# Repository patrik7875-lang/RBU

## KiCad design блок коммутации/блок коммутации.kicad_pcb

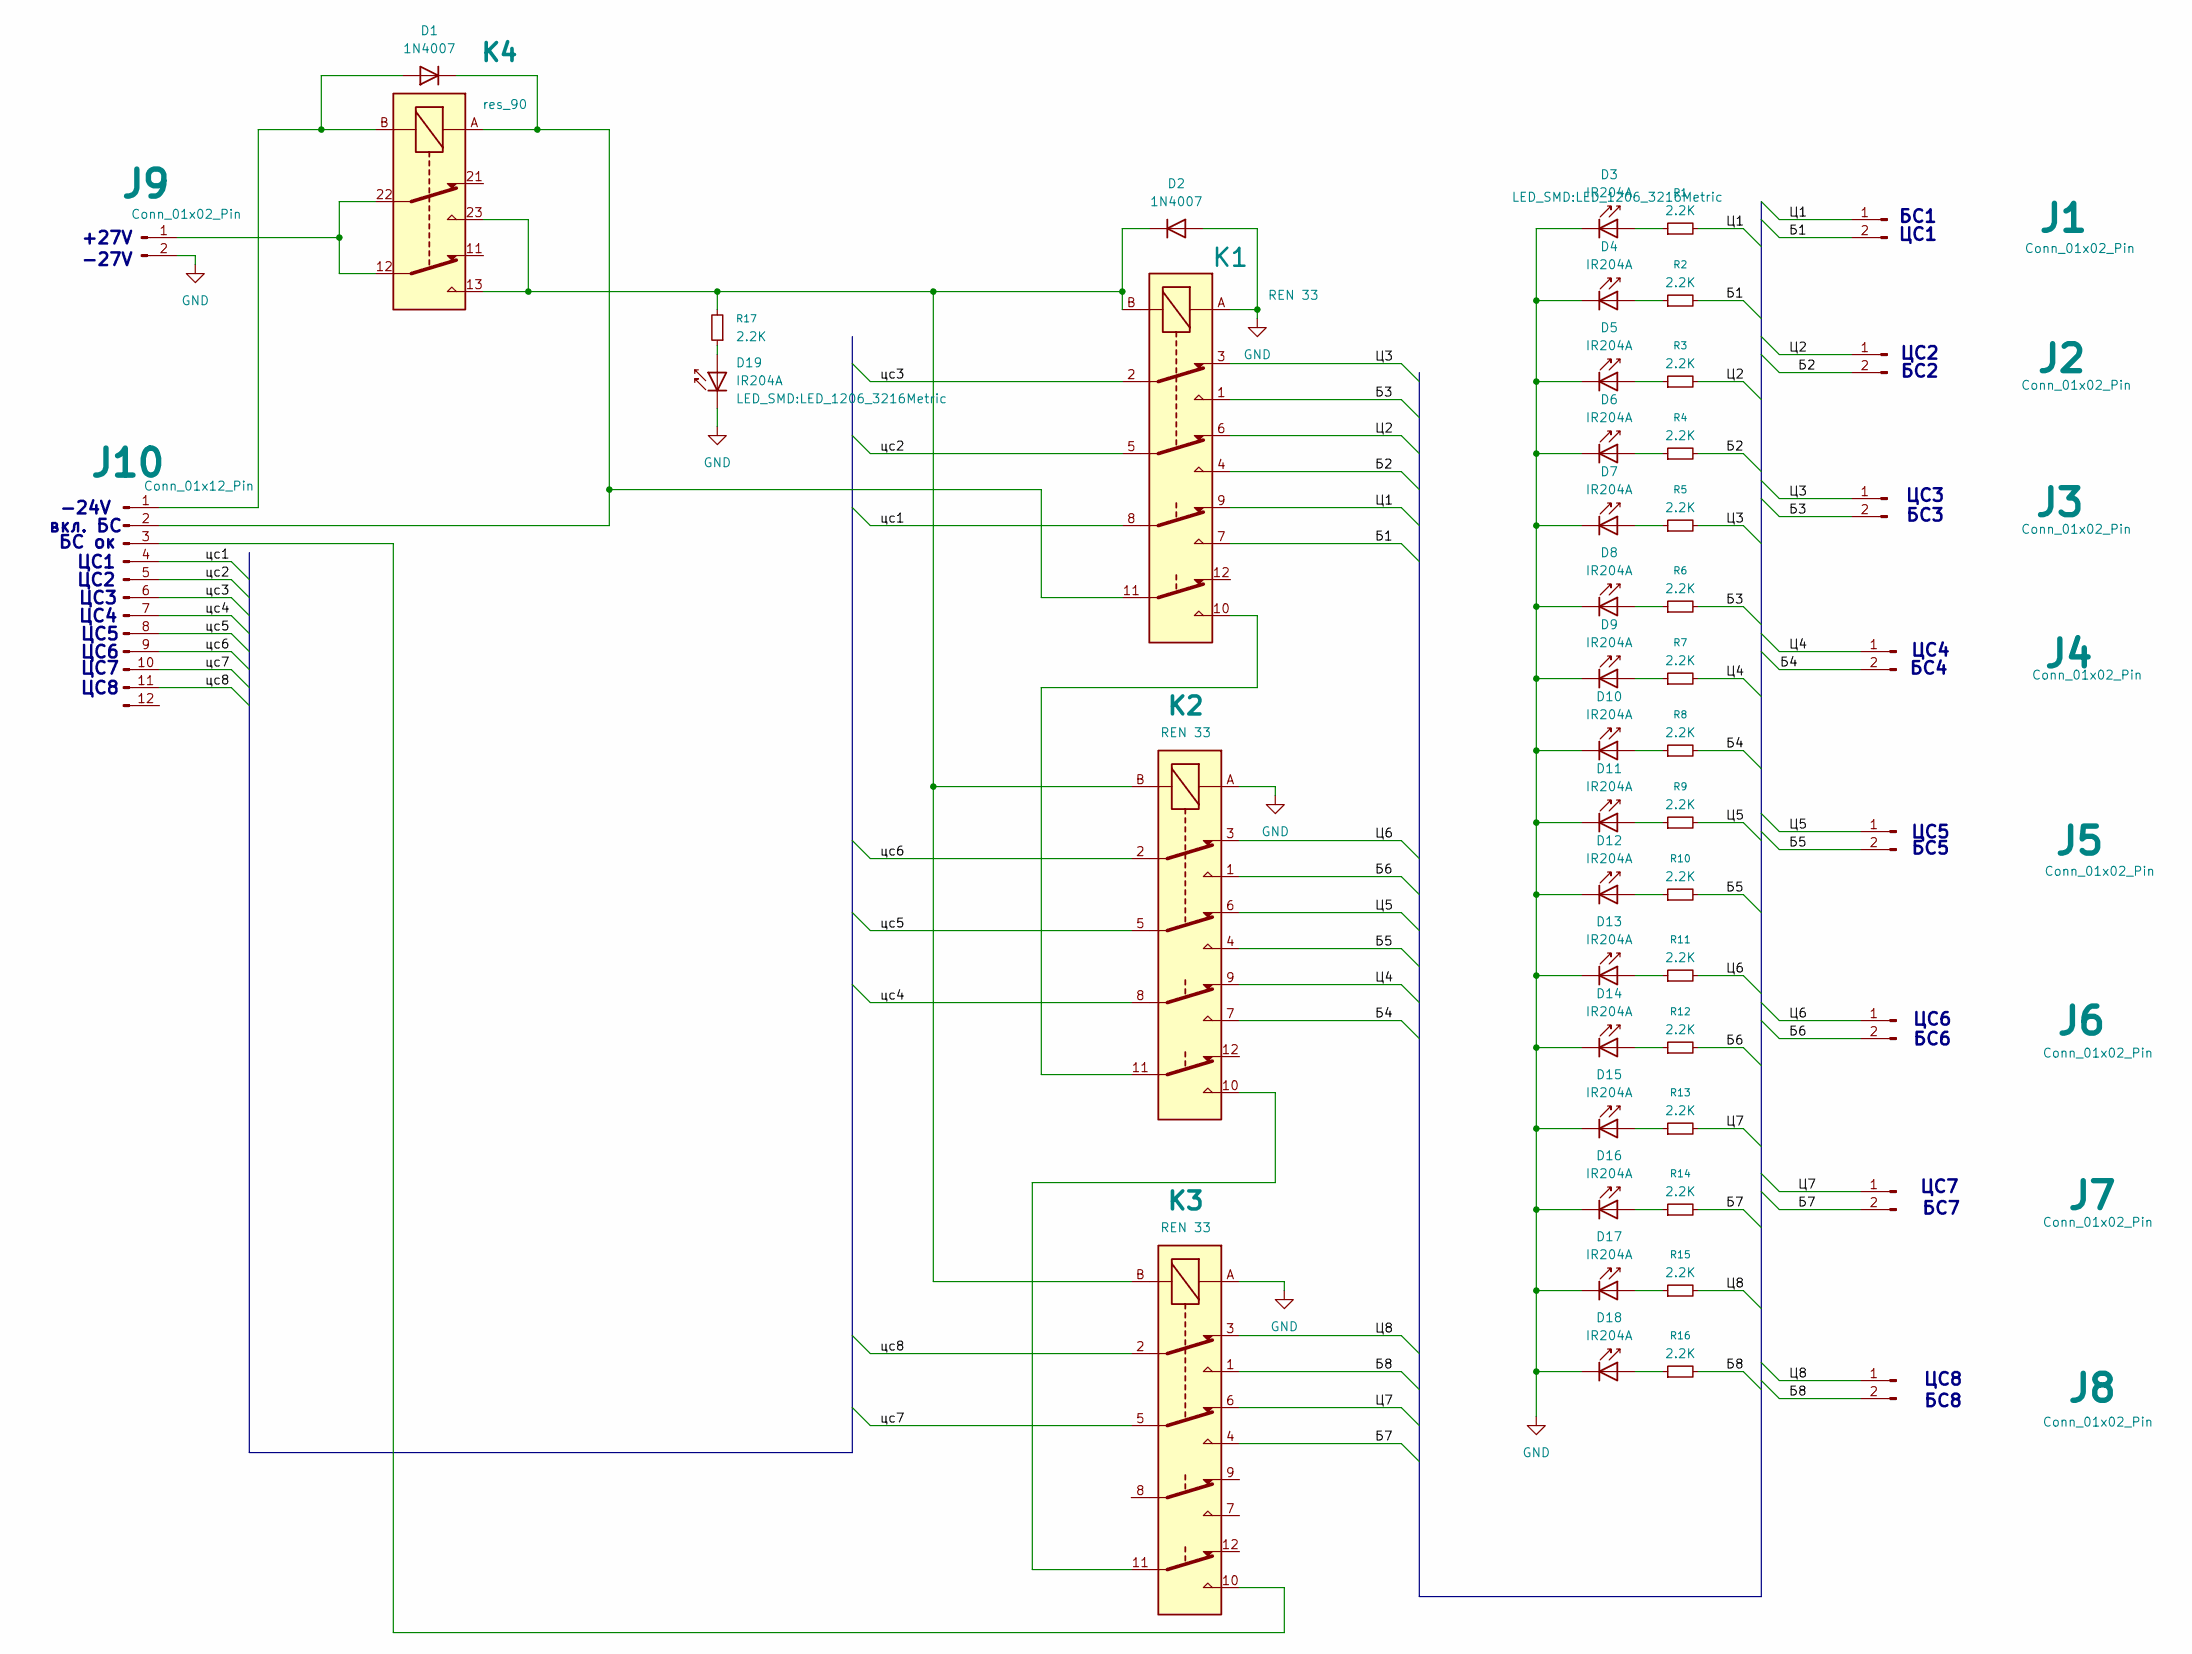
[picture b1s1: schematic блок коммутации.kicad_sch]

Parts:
D1, D2: 1N4007; D_DO-41_SOD81_P10.16mm_Horizontal
D3, D4, D5, D6, D7, D8, D9, D10, D11, D12, D13, D14, D15, D16, D17, D18, D19: IR204A; LED_1206_3216Metric
J1, J2, J3, J4, J5, J6, J7, J8, J9: Conn_01x02_Pin; TerminalBlock_Phoenix_MKDS-1,5-2_1x02_P5.00mm_Horizontal
J10: Conn_01x12_Pin; TerminalBlock_Phoenix_PT-1,5-12-5.0-H_1x12_P5.00mm_Horizont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
K1, K2, K3: REN 33
K4: res_90; res90
R1, R2, R3, R4, R5, R6, R7, R8, R9, R10, R11, R12, R13, R14, R15, R16, R17: 2.2K; R_1206_3216Metric

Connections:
/Б1: J1.2, K1.7, R2.2
/Б2: J2.2, K1.4, R4.2
/Б3: J3.2, K1.1, R6.2
/Б4: J4.2, K2.7, R8.2
/Б5: J5.2, K2.4, R10.2
/Б6: J6.2, K2.1, R12.2
/Б7: J7.2, K3.4, R14.2
/Б8: J8.2, K3.1, R16.2
/Ц1: J1.1, K1.9, R1.2
/Ц2: J2.1, K1.6, R3.2
/Ц3: J3.1, K1.3, R5.2
/Ц4: J4.1, K2.9, R7.2
/Ц5: J5.1, K2.6, R9.2
/Ц6: J6.1, K2.3, R11.2
/Ц7: J7.1, K3.6, R13.2
/Ц8: J8.1, K3.3, R15.2
/цс1: J10.4, K1.8
/цс2: J10.5, K1.5
/цс3: J10.6, K1.2
/цс4: J10.7, K2.8
/цс5: J10.8, K2.5
/цс6: J10.9, K2.2
/цс7: J10.10, K3.5
/цс8: J10.11, K3.2
GND: D2.2 (A), D3.1 (K), D4.1 (K), D5.1 (K), D6.1 (K), D7.1 (K), D8.1 (K), D9.1 (K), D10.1 (K), D11.1 (K), D12.1 (K), D13.1 (K), D14.1 (K), D15.1 (K), D16.1 (K), D17.1 (K), D18.1 (K), D19.1 (K), J9.2, K1.A, K2.A, K3.A
unnamed: D1.2 (A), J10.1, K4.B
unnamed: D1.1 (K), J10.2, K1.11, K4.A
unnamed: D2.1 (K), K1.B, K2.B, K3.B, K4.13, K4.23, R17.2
unnamed: D3.2 (A), R1.1
unnamed: D4.2 (A), R2.1
unnamed: D5.2 (A), R3.1
unnamed: D6.2 (A), R4.1
unnamed: D7.2 (A), R5.1
unnamed: D8.2 (A), R6.1
unnamed: D9.2 (A), R7.1
unnamed: D10.2 (A), R8.1
unnamed: D11.2 (A), R9.1
unnamed: D12.2 (A), R10.1
unnamed: D13.2 (A), R11.1
unnamed: D14.2 (A), R12.1
unnamed: D15.2 (A), R13.1
unnamed: D16.2 (A), R14.1
unnamed: D17.2 (A), R15.1
unnamed: D18.2 (A), R16.1
unnamed: D19.2 (A), R17.1
unnamed: J9.1, K4.12, K4.22
unnamed: J10.3, K3.10
unnamed: K1.10, K2.11
unnamed: K2.10, K3.11

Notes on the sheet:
ЦС7
ЦС1
ЦС5
-27V
ЦС6
ЦС2
БС3
ЦС3
БС1
БС5
-24V
вкл. БС
+27V
БС4
БС6
ЦС8
БС2
БС ок
ЦС4
БС7
БС8

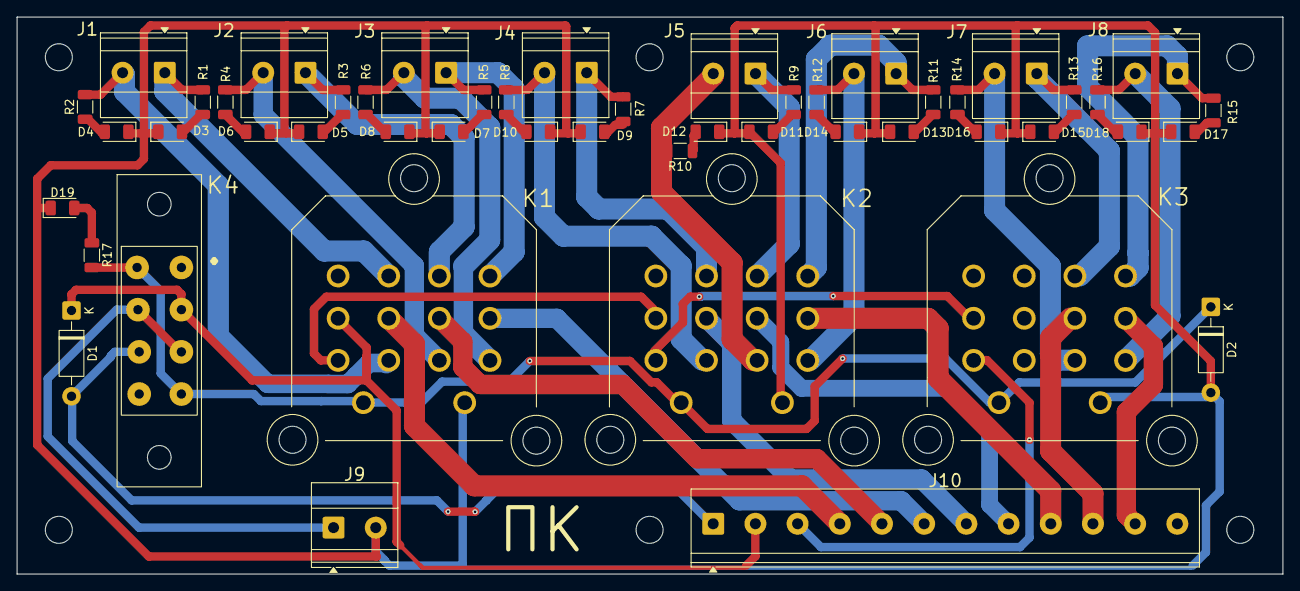
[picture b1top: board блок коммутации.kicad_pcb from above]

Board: 2 copper layers, 150.0 x 66.0 mm, 50 parts (0 on the bottom side), 49 nets.

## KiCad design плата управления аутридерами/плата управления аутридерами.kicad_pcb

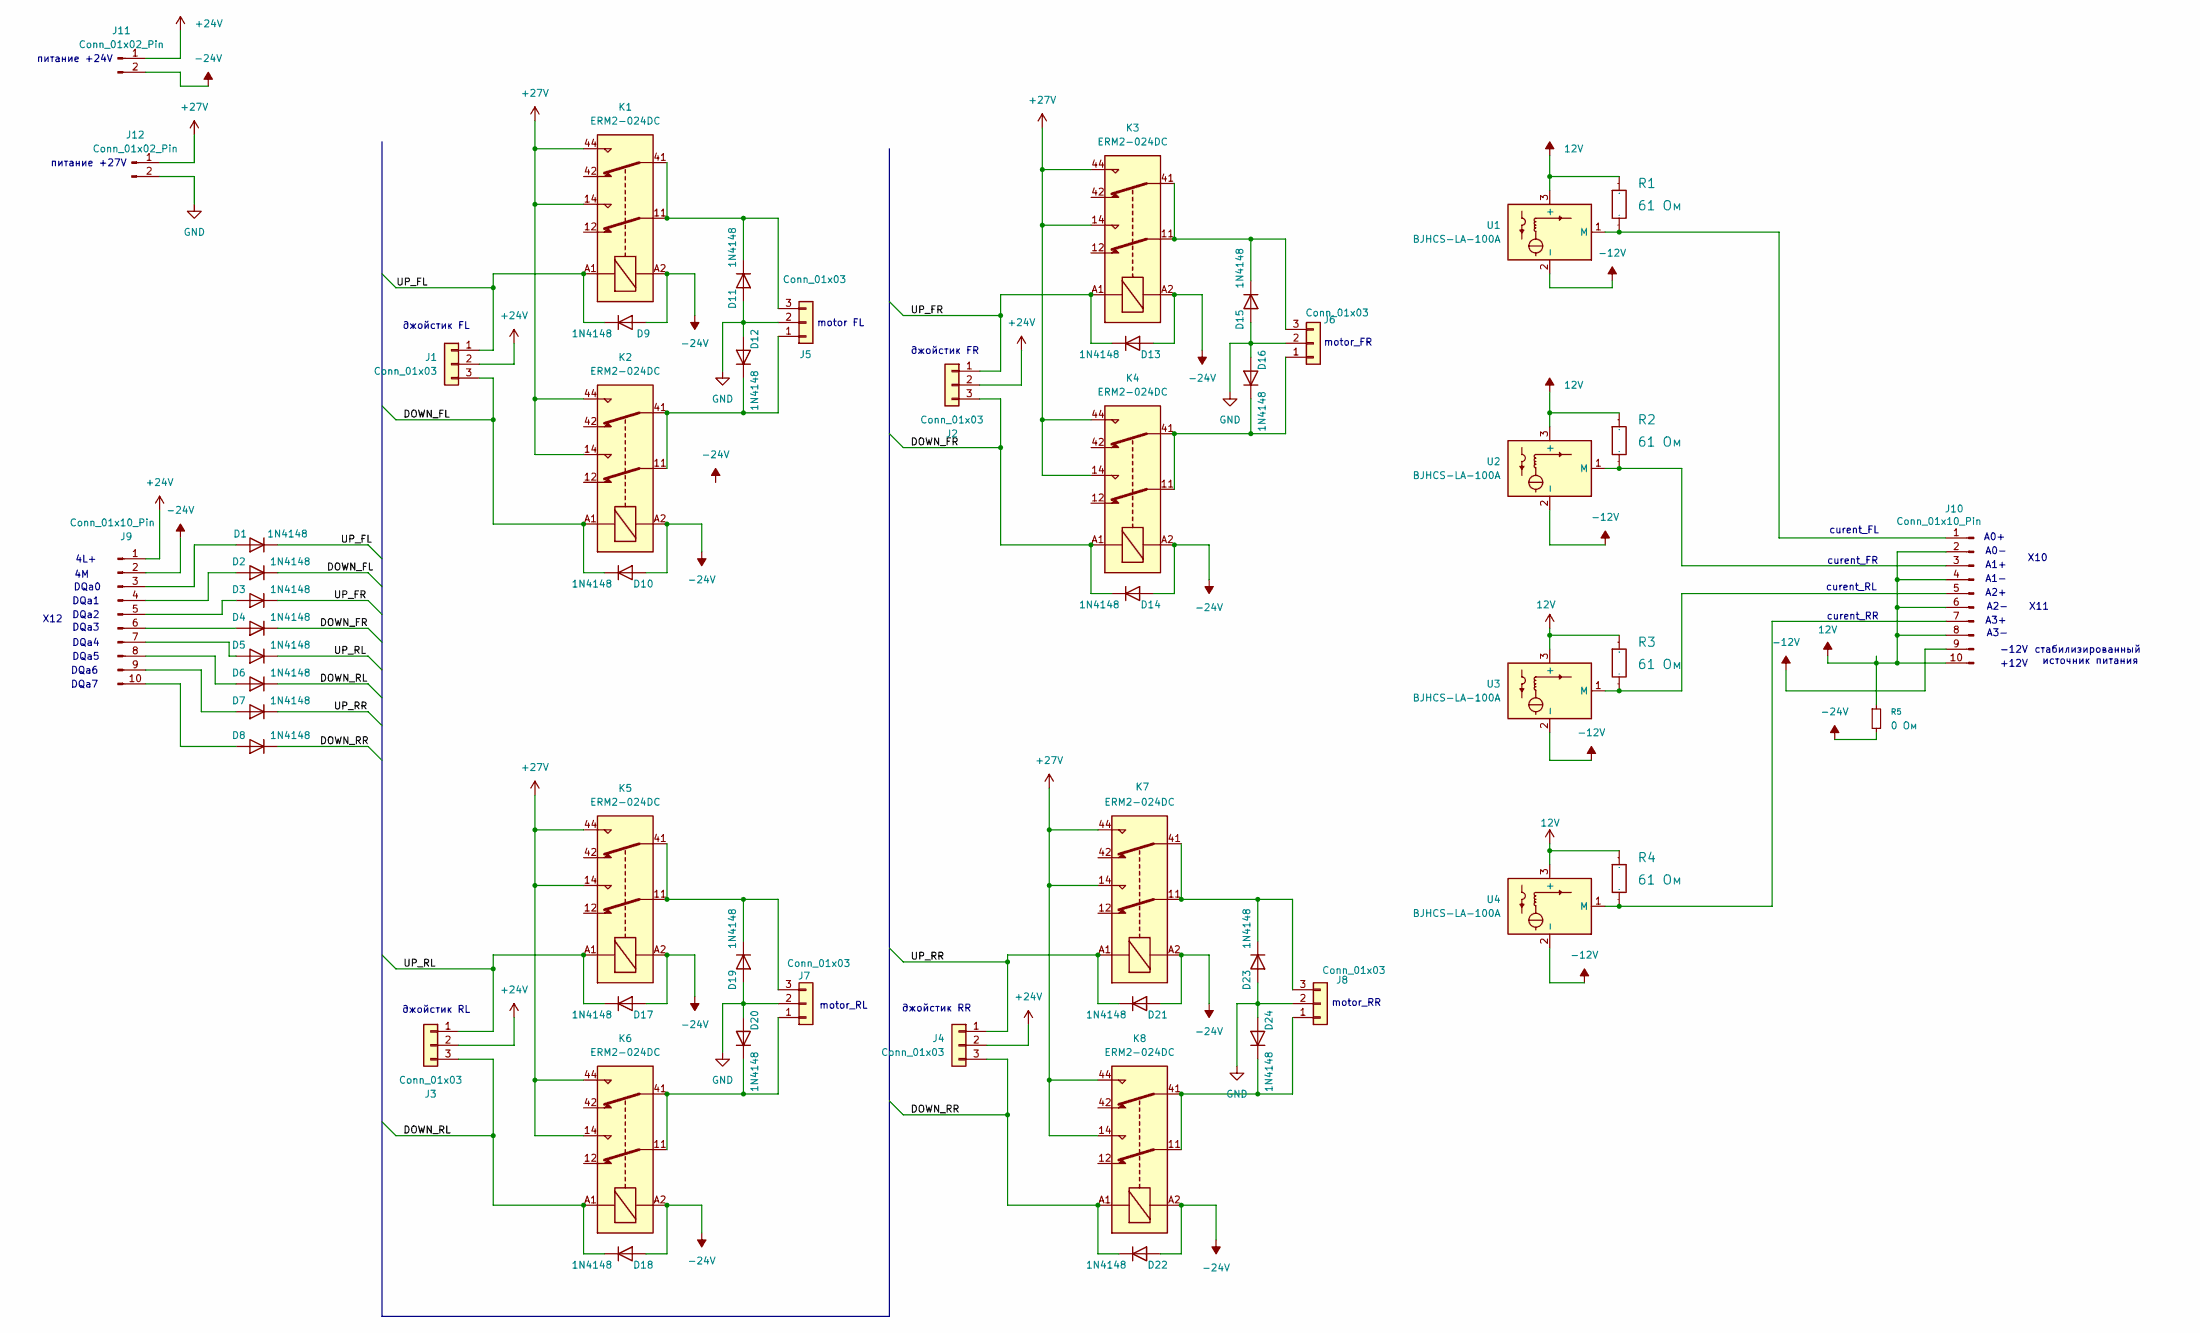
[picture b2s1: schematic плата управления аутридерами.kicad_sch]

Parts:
D1, D2, D3, D4, D5, D6, D7, D8, D9, D10, D11, D12, D13, D14, D15, D16, D17, D18, D19, D20, D21, D22, D23, D24: 1N4148; D_SOD-123
J1, J2, J3, J4, J5, J6, J7, J8: Conn_01x03; Molex_KK-254_AE-6410-03A_1x03_P2.54mm_Vertical
J9, J10: Conn_01x10_Pin; TerminalBlock_Phoenix_MKDS-1-10-3.81_1x10_P3.81mm_Horizontal
J11, J12: Conn_01x02_Pin; TerminalBlock_Phoenix_PT-1,5-2-5.0-H_1x02_P5.00mm_Horizontal
K1, K2, K3, K4, K5, K6, K7, K8: ERM2-024DC
R1, R2, R3, R4: 61 Ом; R_Bare_Metal_Element_L21.3mm_W4.8mm_P20.30mm; Manufacturer Part SC0805J1000F4ANRH
R5: 0 Ом; R_1206_3216Metric
U1, U2, U3, U4: BJHCS-LA-100A

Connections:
12V: J10.2, J10.4, J10.6, J10.8, J10.10, R1.1, R2.1, R3.1, R4.1, R5.1, U1.3 (+), U2.3 (+), U3.3 (+), U4.3 (+)
+24V: J1.2, J2.2, J3.2, J4.2, J9.1, J11.1
+27V: J12.1, K1.14, K1.44, K2.14, K2.44, K3.14, K3.44, K4.14, K4.44, K5.14, K5.44, K6.14, K6.44, K7.14, K7.44, K8.14, K8.44
-12V: J10.9, U1.2 (-), U2.2 (-), U3.2 (-), U4.2 (-)
-24V: D9.2 (A), D10.2 (A), D13.2 (A), D14.2 (A), D17.2 (A), D18.2 (A), D21.2 (A), D22.2 (A), J9.2, J11.2, K1.A2, K2.A2, K3.A2, K4.A2, K5.A2, K6.A2, K7.A2, K8.A2, R5.2
/DOWN_FL: D2.1 (K), D10.1 (K), J1.3, K2.A1
/DOWN_FR: D4.1 (K), D14.1 (K), J2.3, K4.A1
/DOWN_RL: D6.1 (K), D18.1 (K), J3.3, K6.A1
/DOWN_RR: D8.1 (K), D22.1 (K), J4.3, K8.A1
/UP_FL: D1.1 (K), D9.1 (K), J1.1, K1.A1
/UP_FR: D3.1 (K), D13.1 (K), J2.1, K3.A1
/UP_RL: D5.1 (K), D17.1 (K), J3.1, K5.A1
/UP_RR: D7.1 (K), D21.1 (K), J4.1, K7.A1
GND: D11.2 (A), D12.2 (A), D15.2 (A), D16.2 (A), D19.2 (A), D20.2 (A), D23.2 (A), D24.2 (A), J5.2, J6.2, J7.2, J8.2, J12.2
unnamed: D1.2 (A), J9.3
unnamed: D2.2 (A), J9.4
unnamed: D3.2 (A), J9.5
unnamed: D4.2 (A), J9.6
unnamed: D5.2 (A), J9.7
unnamed: D6.2 (A), J9.8
unnamed: D7.2 (A), J9.9
unnamed: D8.2 (A), J9.10
unnamed: D11.1 (K), J5.3, K1.11, K1.41
unnamed: D12.1 (K), J5.1, K2.11, K2.41
unnamed: D15.1 (K), J6.3, K3.11, K3.41
unnamed: D16.1 (K), J6.1, K4.11, K4.41
unnamed: D19.1 (K), J7.3, K5.11, K5.41
unnamed: D20.1 (K), J7.1, K6.11, K6.41
unnamed: D23.1 (K), J8.3, K7.11, K7.41
unnamed: D24.1 (K), J8.1, K8.11, K8.41
unnamed: J10.1, R1.2, U1.1 (M)
unnamed: J10.3, R2.2, U2.1 (M)
unnamed: J10.5, R3.2, U3.1 (M)
unnamed: J10.7, R4.2, U4.1 (M)

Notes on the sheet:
джойстик FL
DQa6
джойстик RL
DQa0
джойстик RR
curent_RR
DQa5
curent_FL
DQa4
-12V
A1-
DQa1
motor_FR
curent_RL
питание +27V
X11
motor_RR
DQa3
A3-
джойстик FR
DQa2
стабилизированный источник питания
X12
4L+
motor FL
+12V
DQa7
motor_RL
A0+
A2-
A1+
A0-
X10
curent_FR
питание +24V
A3+
A2+

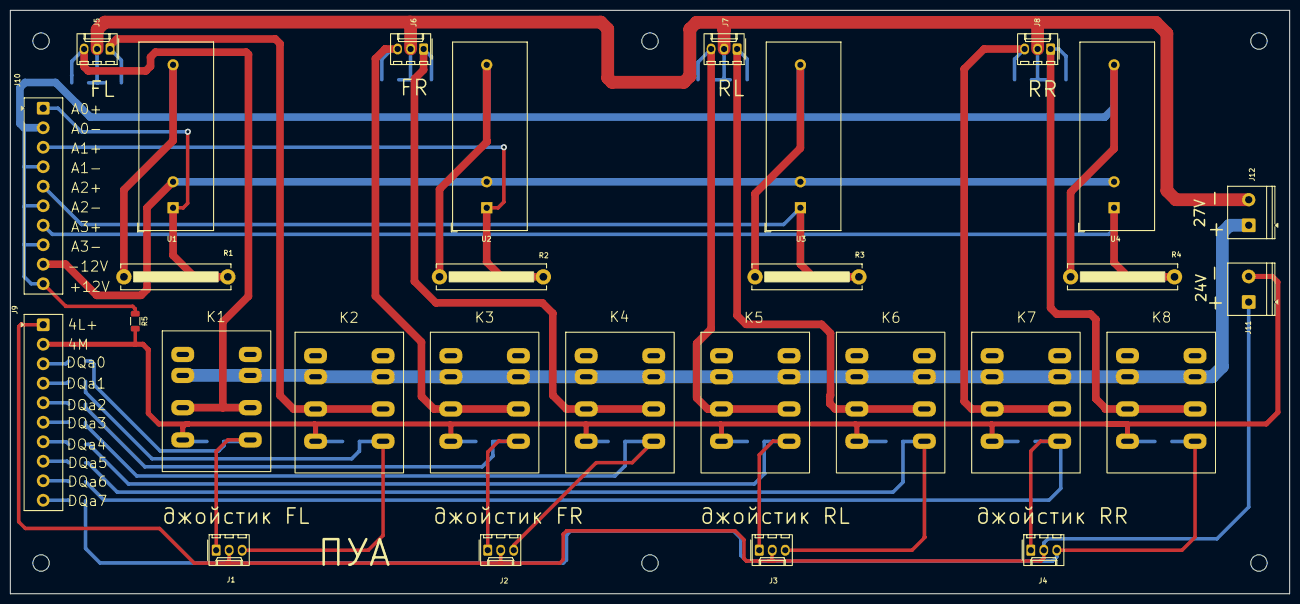
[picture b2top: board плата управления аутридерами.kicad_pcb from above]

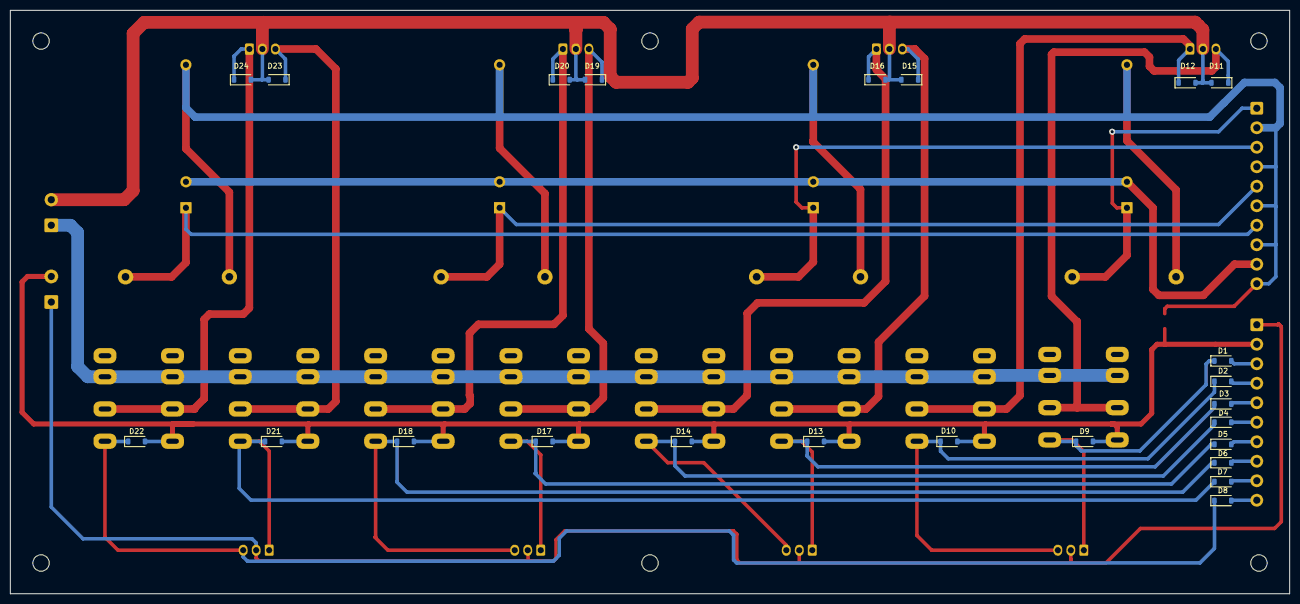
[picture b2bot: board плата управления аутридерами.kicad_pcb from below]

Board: 2 copper layers, 250.0 x 114.0 mm, 53 parts (24 on the bottom side), 34 nets.

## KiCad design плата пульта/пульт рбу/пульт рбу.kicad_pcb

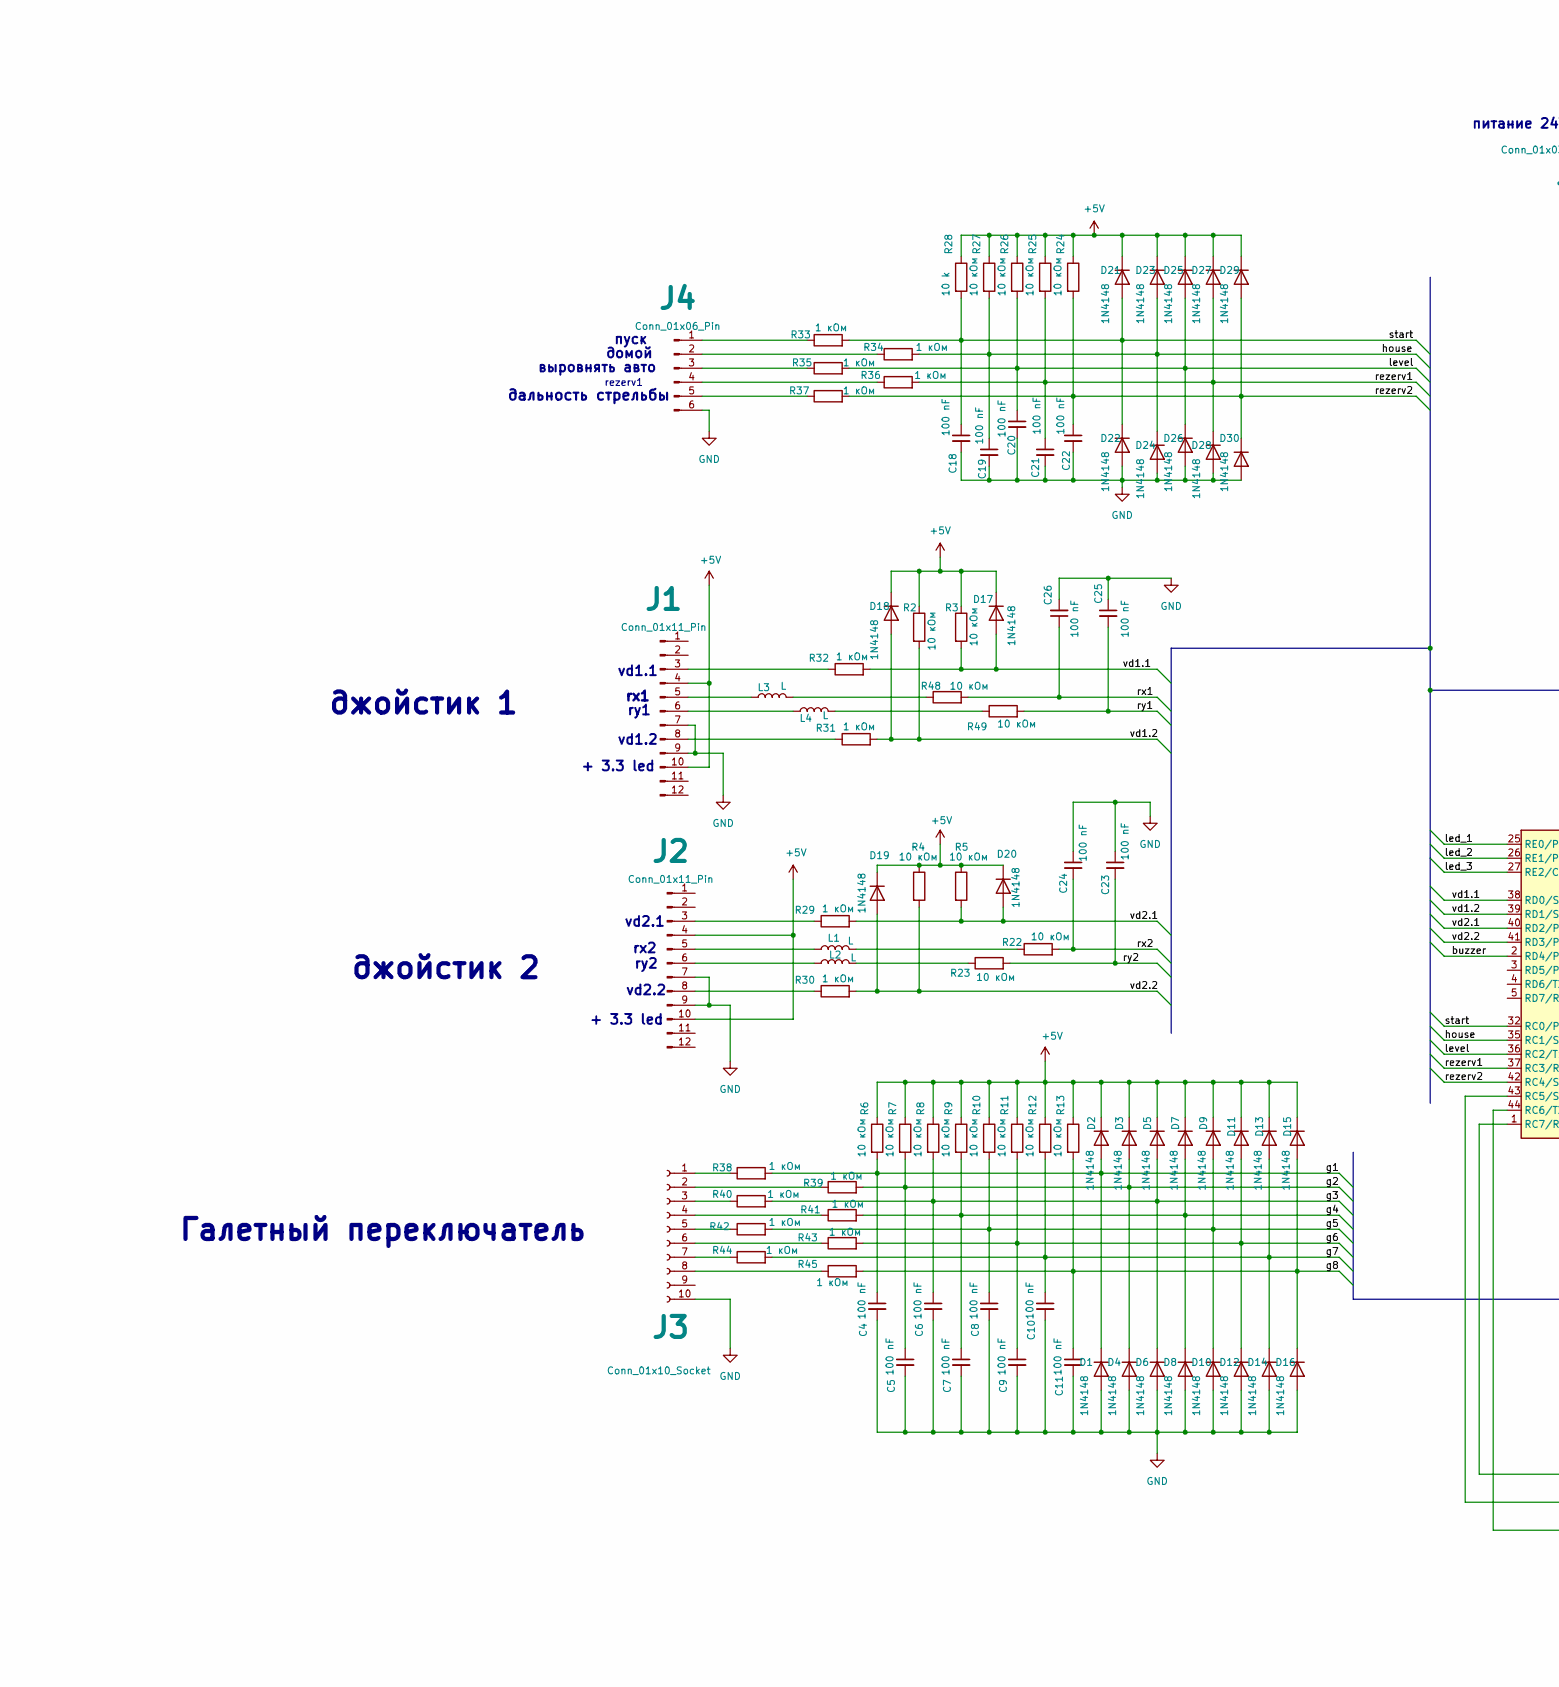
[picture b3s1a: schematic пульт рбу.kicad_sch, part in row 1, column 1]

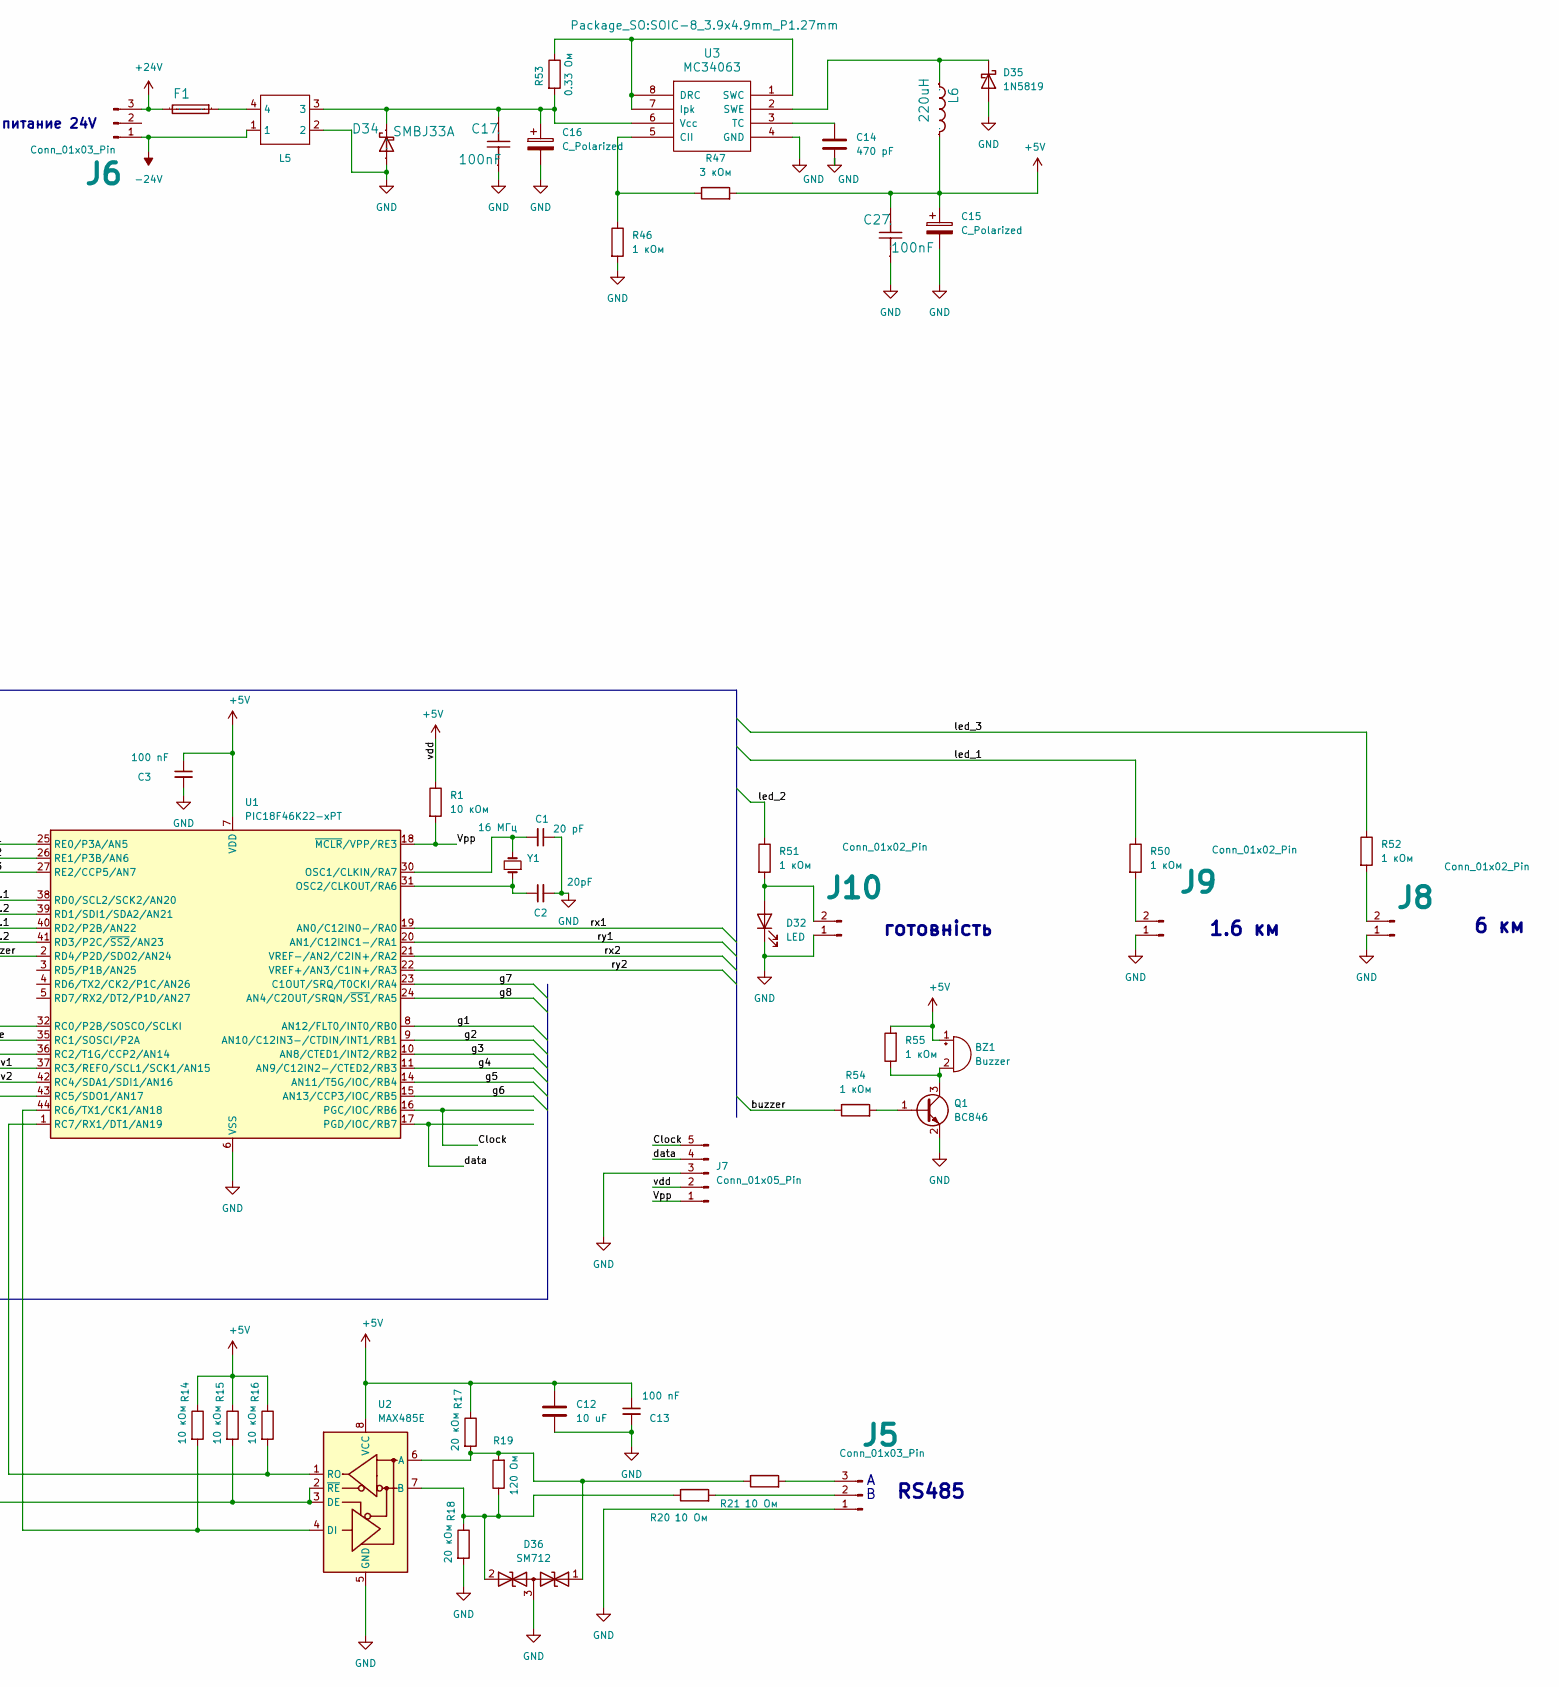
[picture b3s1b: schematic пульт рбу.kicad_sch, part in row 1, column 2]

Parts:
BZ1: Buzzer; Buzzer_12x9.5RM7.6
C1: 20 pF; C_0805_2012Metric
C2: 20pF; C_0805_2012Metric
C3, C4, C5, C6, C7, C8, C9, C10, C11, C13, C18, C19, C20, C21, C22, C23, C24, C25, C26: 100 nF; C_1206_3216Metric
C12: 10 uF; C_1206_3216Metric
C14: 470 pF; C_0805_2012Metric
C15, C16: C_Polarized; C_Radial_D10.0mm_H16.0mm_P5.00mm
C17, C27: 100nF; C_1206_3216Metric; Manufacturer Part FCC0805B104M500DT
D1, D2, D3, D4, D5, D6, D7, D8, D9, D10, D11, D12, D13, D14, D15, D16, D17, D18, D19, D20, D21, D22, D23, D24, D25, D26, D27, D28, D29, D30: 1N4148; D_SOD-123
D32: LED; LED_1206_3216Metric
D34: SMBJ33A; D_SMB
D35: 1N5819; D_DO-41_SOD81_P10.16mm_Horizontal
D36: SM712; SOT-23
F1: 0.5 A; Fuse_1206_3216Metric; Manufacturer Part JFC2410-0200FS
J1, J2: Conn_01x11_Pin; JST_PH_B12B-PH-K_1x12_P2.00mm_Vertical
J3: Conn_01x10_Socket; Molex_KK-254_AE-6410-10A_1x10_P2.54mm_Vertical
J4: Conn_01x06_Pin; Molex_KK-254_AE-6410-06A_1x06_P2.54mm_Vertical
J5, J6: Conn_01x03_Pin; Molex_KK-254_AE-6410-03A_1x03_P2.54mm_Vertical
J7: Conn_01x05_Pin; PinHeader_1x05_P2.54mm_Vertical
J8, J9, J10: Conn_01x02_Pin; JST_PH_B2B-PH-K_1x02_P2.00mm_Vertical
L1, L2, L3, L4: L; L_0805_2012Metric
L5: SSRH7H-M20016
L6: 220uH; L_Changjiang_FXL0840; Manufacturer Part CYL104R-10UH
Q1: BC846; SOT-23
R1, R4, R5: 10 кОм; Fuse_1206_3216Metric
R2, R3, R6, R7, R8, R9, R10, R11, R12, R13, R14, R15, R16, R24, R25, R26, R27: 10 кОм; R_1206_3216Metric
R17, R18: 20 кОм; R_1206_3216Metric
R19: 120 Ом; R_1206_3216Metric
R20, R21: 10 Ом; R_1206_3216Metric
R22, R23, R48, R49: 10 кОм; R_0805_2012Metric
R28: 10 k; R_1206_3216Metric
R29, R30, R31, R32, R33, R34, R35, R36, R37, R38, R39, R40, R41, R42, R43, R44, R45, R46, R50, R51, R52, R54, R55: 1 кОм; R_0805_2012Metric
R47: 3 кОм; R_0805_2012Metric
R53: 0.33 Ом; R_Axial_DIN0207_L6.3mm_D2.5mm_P2.54mm_Vertical
U1: PIC18F46K22-xPT; TQFP-44_10x10mm_P0.8mm
U2: MAX485E; SOIC-8_3.9x4.9mm_P1.27mm
U3: MC34063; SOIC-8_3.9x4.9mm_P1.27mm
Y1: 16 МГц; Crystal_HC18-U_Vertical

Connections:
+5V: BZ1.1 (+), C3.1, C12.1, C13.1, C15.1, C27.1, D2.1 (K), D3.1 (K), D5.1 (K), D7.1 (K), D9.1 (K), D11.1 (K), D13.1 (K), D15.1 (K), D17.1 (K), D18.1 (K), D19.1 (K), D20.1 (K), D21.1 (K), D23.1 (K), D25.1 (K), D27.1 (K), D29.1 (K), J1.4, J1.10, J2.4, J2.10, J7.2, L6.2, R1.1, R2.1, R3.1, R4.1, R5.1, R6.1, R7.1, R8.1, R9.1, R10.1, R11.1, R12.1, R13.1, R14.1, R15.1, R16.1, R17.1, R24.1, R25.1, R26.1, R27.1, R28.1, R47.2, R55.2, U1.7 (VDD), U1.28 (VDD), U2.8 (VCC)
+24V: F1.2, J6.3
-24V: J6.1, L5.1
/Clock: J7.5, U1.16 (PGC/IOC/RB6)
/Vpp: J7.1, R1.2, U1.18 (~MCLR/VPP/RE3)
/buzzer: R54.1, U1.2 (RD4/P2D/SDO2/AN24)
/data: J7.4, U1.17 (PGD/IOC/RB7)
/g1: C4.1, D1.1 (K), D2.2 (A), R6.2, R38.2, U1.8 (AN12/FLT0/INT0/RB0)
/g2: C5.1, D3.2 (A), D4.1 (K), R7.2, R39.2, U1.9 (AN10/C12IN3-/CTDIN/INT1/RB1)
/g3: C6.1, D5.2 (A), D6.1 (K), R8.2, R40.2, U1.10 (AN8/CTED1/INT2/RB2)
/g4: C7.1, D7.2 (A), D8.1 (K), R9.2, R41.2, U1.11 (AN9/C12IN2-/CTED2/RB3)
/g5: C8.1, D9.2 (A), D10.1 (K), R10.2, R42.2, U1.14 (AN11/T5G/IOC/RB4)
/g6: C9.1, D11.2 (A), D12.1 (K), R11.2, R43.2, U1.15 (AN13/CCP3/IOC/RB5)
/g7: C10.1, D13.2 (A), D14.1 (K), R12.2, R44.2, U1.23 (C1OUT/SRQ/T0CKI/RA4)
/g8: C11.1, D15.2 (A), D16.1 (K), R13.2, R45.2, U1.24 (AN4/C2OUT/SRQN/~SS1/RA5)
/house: C19.1, D23.2 (A), D24.1 (K), R27.2, R34.2, U1.35 (RC1/SOSCI/P2A)
/led_1: R50.1, U1.25 (RE0/P3A/AN5)
/led_2: R51.1, U1.26 (RE1/P3B/AN6)
/led_3: R52.1, U1.27 (RE2/CCP5/AN7)
/level: C20.1, D25.2 (A), D26.1 (K), R26.2, R35.2, U1.36 (RC2/T1G/CCP2/AN14)
/rezerv1: C21.1, D27.2 (A), D28.1 (K), R25.2, R36.2, U1.37 (RC3/REFO/SCL1/SCK1/AN15)
/rezerv2: C22.1, D29.2 (A), D30.1 (K), R24.2, R37.2, U1.42 (RC4/SDA1/SDI1/AN16)
/rx1: C26.1, R48.2, U1.19 (AN0/C12IN0-/RA0)
/rx2: C24.2, R22.2, U1.21 (VREF-/AN2/C2IN+/RA2)
/ry1: C25.2, R49.2, U1.20 (AN1/C12INC1-/RA1)
/ry2: C23.2, R23.2, U1.22 (VREF+/AN3/C1IN+/RA3)
/start: C18.1, D21.2 (A), D22.1 (K), R28.2, R33.2, U1.32 (RC0/P2B/SOSCO/SCLKI)
/vd1.1: D17.2 (A), R3.2, R32.2, U1.38 (RD0/SCL2/SCK2/AN20)
/vd1.2: D18.2 (A), R2.2, R31.2, U1.39 (RD1/SDI1/SDA2/AN21)
/vd2.1: D20.2 (A), R5.2, R29.2, U1.40 (RD2/P2B/AN22)
/vd2.2: D19.2 (A), R4.2, R30.2, U1.41 (RD3/P2C/~SS2/AN23)
GND: C1.1, C2.2, C3.2, C4.2, C5.2, C6.2, C7.2, C8.2, C9.2, C10.2, C11.2, C12.2, C13.2, C14.2, C15.2, C16.2, C17.2, C18.2, C19.2, C20.2, C21.2, C22.2, C23.1, C24.1, C25.1, C26.2, C27.2, D1.2 (A), D4.2 (A), D6.2 (A), D8.2 (A), D10.2 (A), D12.2 (A), D14.2 (A), D16.2 (A), D22.2 (A), D24.2 (A), D26.2 (A), D28.2 (A), D30.2 (A), D32.1 (K), D34.2 (A), D35.2 (A), D36.3 (common), J1.7, J1.9, J2.7, J2.9, J3.10, J4.6, J5.1, J7.3, J8.1, J9.1, J10.1, L5.2, Q1.2 (E), R18.2, R46.2, U1.6 (VSS), U1.29 (VSS), U2.5 (GND), U3.4 (GND)
unnamed: BZ1.2 (-), Q1.3 (C), R55.1
unnamed: D32.2 (A), J10.2, R51.2
unnamed: C16.1, C17.1, D34.1 (K), L5.3, R53.2, U3.6 (Vcc)
unnamed: D35.1 (K), L6.1, U3.2 (SWE)
unnamed: D36.1 (A1), R17.2, R19.2, R21.1, U2.6 (A)
unnamed: D36.2 (A2), R18.1, R19.1, R20.1, U2.7 (B)
unnamed: F1.1, L5.4
unnamed: J1.3, R32.1
unnamed: J1.5, L3.1
unnamed: J1.6, L4.1
unnamed: J1.8, R31.1
unnamed: J2.3, R29.1
unnamed: J2.5, L1.1
unnamed: J2.6, L2.1
unnamed: J2.8, R30.1
unnamed: J3.1, R38.1
unnamed: J3.2, R39.1
unnamed: J3.3, R40.1
unnamed: J3.4, R41.1
unnamed: J3.5, R42.1
unnamed: J3.6, R43.1
unnamed: J3.7, R44.1
unnamed: J3.8, R45.1
unnamed: J4.1, R33.1
unnamed: J4.2, R34.1
unnamed: J4.3, R35.1
unnamed: J4.4, R36.1
unnamed: J4.5, R37.1
unnamed: J5.2, R20.2
unnamed: J5.3, R21.2
unnamed: J8.2, R52.2
unnamed: J9.2, R50.2
unnamed: L1.2, R22.1
unnamed: L2.2, R23.1
unnamed: L3.2, R48.1
unnamed: L4.2, R49.1
unnamed: Q1.1 (B), R54.2
unnamed: C1.2, U1.30 (OSC1/CLKIN/RA7), Y1.2
unnamed: C2.1, U1.31 (OSC2/CLKOUT/RA6), Y1.1
unnamed: R15.2, U1.43 (RC5/SDO1/AN17), U2.2 (~RE), U2.3 (DE)
unnamed: R14.2, U1.44 (RC6/TX1/CK1/AN18), U2.4 (DI)
unnamed: R16.2, U1.1 (RC7/RX1/DT1/AN19), U2.1 (RO)
unnamed: R46.1, R47.1, U3.5 (CII)
unnamed: R53.1, U3.1 (SWC), U3.7 (Ipk), U3.8 (DRC)
unnamed: C14.1, U3.3 (TC)

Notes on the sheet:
vd1.2
RS485
выровнять авто
+ 3.3 led
джойстик 1
домой
ry1
vd2.2
vd1.1
rx1
Галетный переключатель
джойстик 2
дальность стрельбы
vd2.1
1.6 км
rx2
питание 24V
6 км
ry2
пуск
rezerv1
готовнiсть
